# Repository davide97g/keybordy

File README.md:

# keybordy

A small keyboard built on a classic ESP32 DevKit: eight MX-style switches wired with jumpers only, and a rotary encoder to add later.

- `firmware/keys8/`: current firmware. Reads 8 keys, acts as a Bluetooth LE keyboard named `keybordy` that presses F13–F20, and prints `key N down` / `key N up` on serial at 115200. Also holds the Wokwi `diagram.json`.
- `host/`: Mac side. Hammerspoon maps F13–F20 to actions and serves a keymap editor on http://localhost:7373 (`host/ui/`).
- `firmware/switches_oled/`, `firmware/rotary_oled/`: earlier sketches with the SSD1306 OLED.
- `sim/`: fully local simulator, a vendored fork of Velxio (AGPLv3) in Docker, with a local Postgres for saved projects. Run `just sim-fetch-qemu` once, then `just sim-up` and open http://localhost:3080/editor?project=keys8. See `sim/README.md`.
- `pcb/`: rev A carrier PCB (KiCad 10, generated by `pcb/build.py`). Hotswap sockets for the 8 keys, female headers for the DevKit, OLED and rotary. Pin map, paper check and JLCPCB ordering steps are in `pcb/README.md`.
- `docs/`: board and bench notes.
- `guide/`: interactive wiring guide (Vite + React).

## Tooling

Tasks live in the root `justfile` (`just` lists them); tool versions are pinned in `mise.toml` (Bun, Node, Python, uv, just). Frontends use Bun (`bun.lock`), the simulator backend uses uv (`uv.lock`).

```
just install         # bun + uv dependencies
just dev             # simulator with backend hot reload + UI on http://localhost:5173
just test            # backend (incl. Postgres) + frontend tests
just fw-flash        # compile and flash keys8
```

## Wiring

No breadboard, so every board pin takes one jumper and each switch gets two pins: leg A to an input with the internal pull-up, leg B to ground. K1 uses a real `GND` pin. K2–K8 use GPIOs the firmware holds LOW.

| Key | Leg A | Leg B |
|---|---|---|
| K1 | GPIO32 | GND |
| K2 | GPIO33 | GPIO25 |
| K3 | GPIO14 | GPIO26 |
| K4 | GPIO13 | GPIO27 |
| K5 | GPIO4 | GPIO16 |
| K6 | GPIO18 | GPIO17 |
| K7 | GPIO19 | GPIO21 |
| K8 | GPIO23 | GPIO22 |
| Rotary (later) | CLK 34, DT 35, SW 39 | `+` to 3V3, GND to the second GND |

## Actions on the Mac

No server to run and no USB needed once flashed: the board only needs power (USB charger or power bank). It pairs as a Bluetooth keyboard, and Hammerspoon turns each key into an action.

1. `just fw-flash`, then power the board anywhere in Bluetooth range.
2. System Settings > Bluetooth: connect `keybordy` (no PIN). The Mac reconnects on its own after that.
3. `just host-install`: installs Hammerspoon into `~/Applications` (no sudo), links `host/hammerspoon/keybordy.lua` into `~/.hammerspoon`, starts it.
4. `just keymap` (or the ⌨︎ menu-bar item > Open keymap editor) opens http://localhost:7373.

The keymap editor shows the eight caps with their current action, lets you pick an action per key and try it before saving: ▶ on a cap (or Test) simulates a press with the unsaved version, and Activity lists every press, real or simulated, with the command output or the error. Save (⌘S) writes `~/.config/keybordy/keymap.json`; hand edits to that file load live too. `host/keymap.default.json` seeds it on first run.

| Action | Does | |
|---|---|---|
| Open app | launch or focus an app (picker with icons) | |
| Terminal | new Ghostty window in a folder, typing a command such as `claude` | |
| Shell command | `zsh -lc` in the background, output in Activity | |
| Open URL | any URL or app scheme (`obsidian://`, `raycast://`) | |
| Shortcut | `shortcuts run <name>` from the Shortcuts app | |
| Key combo | send e.g. ⇧⌘4 to the frontmost app (recorder included) | Accessibility |
| Type text | type a snippet | Accessibility |
| Media key | play/pause, next, volume, brightness | Accessibility |

Hotkeys need no permission. The last three need Hammerspoon in System Settings > Privacy & Security > Accessibility; the editor's `accessibility off · allow` chip opens that prompt. The first Terminal action asks to let Hammerspoon control Ghostty.

The editor is served by Hammerspoon on loopback only. Because it can run shell commands, every API call needs the token embedded in its page, and requests with a foreign `Host` or `Origin` are refused.

## Flash

```
just fw-flash        # arduino-cli compile --upload -p /dev/cu.usbserial-0001 --fqbn esp32:esp32:esp32 firmware/keys8
just fw-monitor
```

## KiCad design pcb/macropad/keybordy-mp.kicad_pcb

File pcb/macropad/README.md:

# keybordy MP PCB, rev A

A 2-layer board, 126.3 × 131.06 mm, for the keybordy MP macropad (`docs/macropad.md`). It is generated from `layout/macropad.json` and `layout/pins.json` by `build.py`. The schematic is in that script too: `parts()` lists every footprint with its pads' nets.

```sh
just mp-pcb          # place, Freerouting (5–20 min), DRC, then fab files into pcb/macropad/fab/
just mp-pcb-fab      # DRC + fab files only, after editing the board by hand in KiCad
just mp-pcb-open     # open in KiCad 10
```

Routing uses Freerouting 1.9.0 (`~/.local/share/freerouting/freerouting-1.9.0.jar`, Java 21+). Version 2.5 oscillates on this board and leaves about 30 connections unrouted. 1.9 is not deterministic either: a run leaves 0 to about 7 connections, so `route` tries up to four times and keeps the best session. A few stubs round the 0.5 mm-pitch amp and charger pins are drawn by hand in `place()`. After routing, `pour` fills GND on both layers and adds stitching vias on a 4 mm grid, plus one in any pour fragment the grid missed. `fab` fails on any DRC error or unconnected item. Silkscreen warnings and one starved thermal (an encoder GND pin, which is also on a routed track) do not block it.

## What is on it

All SMD parts are on the bottom, the same side as the hotswap sockets, so JLCPCB assembles one side.

- ESP32-S3-WROOM-1-N16R8. The antenna is flush with the rear edge, with no copper over it or within 15 mm either side.
- USB-C (USB 2.0) with 5.1k CC pull-downs and USBLC6 ESD protection.
- BQ24075 power-path charger.
  - Input limit about 860 mA (RILIM 1.8k). Charge current about 490 mA (RISET 1.8k).
  - TS has a fixed 10k because the cell has no NTC. Safety timer at its default.
  - The PWR switch drives SYSOFF. Off disconnects the battery; USB still powers the board, but the BQ24075 does not charge while SYSOFF is high, so leave PWR on to charge.
- AP2112K 3.3 V LDO, fed from the charger's OUT.
- MAX98357A amp on OUT, next to the speaker pads. GPIO46 drives SD_MODE high, which selects the left channel.
- ICS-43434 mic. Its port is a hole through the board under the deck's mic hole.
  - The MIC switch feeds its VDD from 3V3, or grounds it.
  - 1k resistors on its WS and SCK limit the current into it while it is off and the amp is using the shared clocks.
- Reverse-mount red LED on GPIO45, shining up through its hole.
- 22 Kailh hotswap sockets with 1N4148W diodes (COL2ROW).
- 3 encoders. A/B have 10k pull-ups. Each push has a diode into matrix row 4.
- BOOT and RST buttons. They are on the bottom, so they are only reachable with the case open. Normal flashing over native USB needs neither.
- Battery voltage on GPIO1 through a 100k/100k divider. Charge status on GPIO44.

## Ordering at JLCPCB

1. Upload `fab/keybordy-mp-gerbers.zip`. The viewer should show 2 layers and 126.3 × 131.06 mm. Keep FR-4, 1.6 mm, 1 oz and HASL lead-free.
2. Turn on PCB Assembly and choose the **Bottom side**. If Economic will not take a bottom-side job, pick Standard.
3. Assembly quantity: 2 is the minimum. Upload `fab/keybordy-mp-bom.csv` and `fab/keybordy-mp-cpl.csv`.
4. In the placement preview, check every polarised part against its silkscreen dot or bar before paying. JLC's rotation offsets differ from KiCad's. Check:
   - U1 to U6, pin 1.
   - D1–D33, cathode bar toward the row net.
   - D30, the LED.
   - J1, the USB-C mouth at the rear edge.
   - J2, the battery connector. Its opening faces the battery.
5. Stock risks as of 2026-10-07:
   - ICS-43434 (C5656610): about 1.4k in stock.
   - The ESP32-S3 module shows 0 at LCSC but 28k in JLC's own assembly stock.
   - Every IC is an Extended part, so each one adds a loading fee.

The BOM leaves out the parts you solder yourself, listed below.

## Solder yourself

| Part | Where | Notes |
|---|---|---|
| 3 × encoder | top, E1–E3 | Bourns PEC11R-4220F-S0024 (LCSC C143797, only a few hundred in stock). The footprint's lug slots also take Alps EC11 encoders such as the Amazon bench ones. |
| OLED, 7 wires | top, J3 at the rear edge | Cut the dupont ends off the Waveshare GH1.25 cable and solder the wires straight in. Pad order is `3V3 GND DIN CLK CS DC RST`, as on the silk. A header does not fit under the plate (3.5 mm). |
| Speaker, 2 wires | top, J4 at the left edge, `+` marked | Cut the PH1.25 plug off. |
| 22 × MX switch | top | They plug into the sockets. No soldering. |
| 2u stabilizer | top, K21 | Cherry PCB screw-in. |
| LiPo | bottom, J2 (JST PH 2.0) | **Check the polarity against the `+` and `-` on the silk before you plug it in.** Amazon cells come wired both ways, and the charger has no reverse-polarity protection. |

## Changes the case needs

- PWR switch moved from x 30 to x 68 in the layout, to the right of the USB-C. At x 30 it collided with the ESP32 module, and it was inside the antenna keep-out. `cad/` reads the layout, so `just cad-build` moves the tray's rear-wall slot. A tray printed before this change has the slot in the wrong place.
- The USB-C mouth sits 0.5 mm past the PCB edge, against the inside of the 3 mm wall. A plug's overmold is about 12.4 × 6.5 mm, so the 10 × 4.2 wall cut-out lets the plug in only about 3.5 mm. To seat the plug fully, widen the cut-out or recess the wall around it.
- The slide-switch levers stick out about 0.85 mm past the PCB edge, which doesn't reach through a 3 mm wall. Thin the wall at the two switch slots, or print a small slider.

## Not verified

- This board is untested. Nothing on it has been through the bench prototype (phase 1) yet. The charger, amp and mic circuits follow their datasheets' typical application circuits.
- The netlist was checked against KiCad's symbol pinouts. There is no separate schematic, so KiCad's ERC never ran.
- The Waveshare OLED's pin order and the speaker plug's wiring come from the listings, not from the parts in hand.

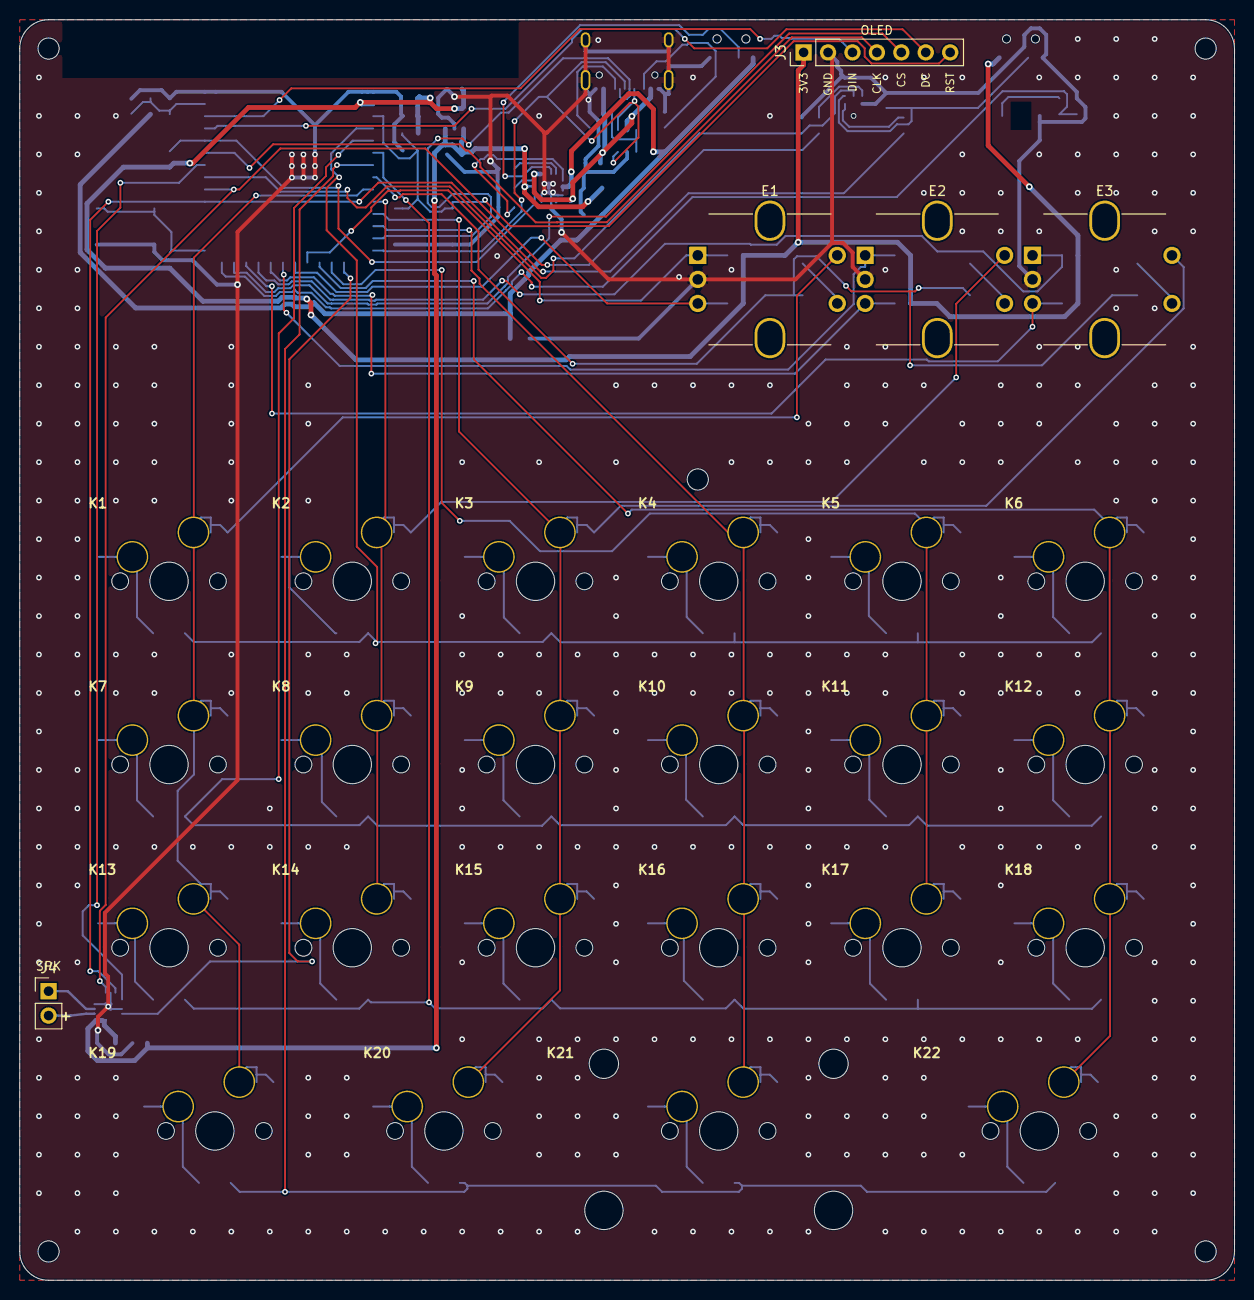
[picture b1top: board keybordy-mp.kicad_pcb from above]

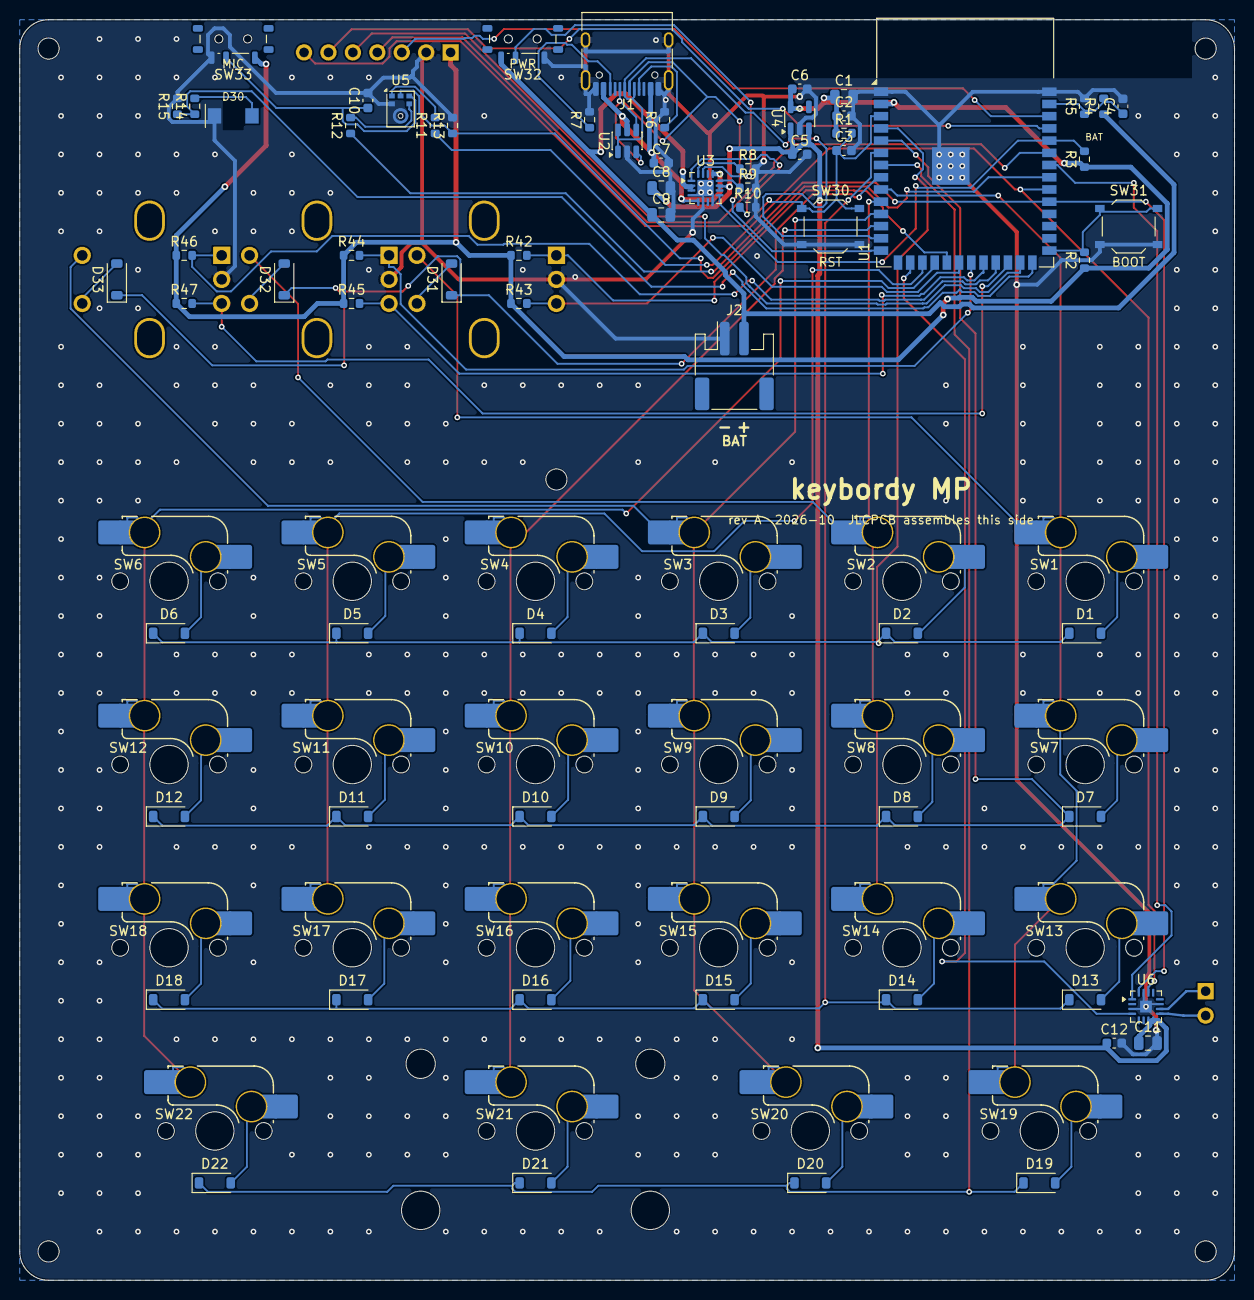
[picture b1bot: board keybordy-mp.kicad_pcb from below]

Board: 2 copper layers, 126.3 x 131.1 mm, 107 parts (93 on the bottom side), 75 nets.

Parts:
C1, C8, C9, C11: 10uF; C_0805_2012Metric
C2, C4, C10, C12: 100nF; C_0603_1608Metric
C3, C5, C6: 1uF; C_0603_1608Metric
C7: 4.7uF; C_0603_1608Metric
D1, D2, D3, D4, D5, D6, D7, D8, D9, D10, D11, D12, D13, D14, D15, D16, D17, D18, D19, D20, D21, D22, D31, D32, D33: 1N4148W; D_SOD-123
D30: LTST-C230KRKT; LED_1206_ReverseMount_LiteOn
E1, E2, E3: PEC11R-4220F-S0024; RotaryEncoder_Bourns_PEC11R_Vertical
H1, H2, H3, H4, H5: M2; MountingHole_2.2mm_M2
J1: TYPE-C-31-M-12; USB_C_Receptacle_HRO_TYPE-C-31-M-12
J2: S2B-PH-SM4-TB; JST_PH_S2B-PH-SM4-TB_1x02-1MP_P2.00mm_Horizontal
J3: OLED wires; PinHeader_1x07_P2.54mm_Vertical
J4: Speaker wires; PinHeader_1x02_P2.54mm_Vertical
R1, R2, R3, R10, R42, R43, R44, R45, R46, R47: 10k; R_0603_1608Metric
R4, R5, R13, R15: 100k; R_0603_1608Metric
R6, R7: 5.1k; R_0603_1608Metric
R8, R9: 1.8k; R_0603_1608Metric
R11, R12, R14: 1k; R_0603_1608Metric
ST1, ST2, ST3, ST4: stab; MountingHole_2.2mm_M2
SW1, SW2, SW3, SW4, SW5, SW6, SW7, SW8, SW9, SW10, SW11, SW12, SW13, SW14, SW15, SW16, SW17, SW18, SW19, SW20, SW21, SW22: Kailh MX hotswap; SW_MX_HS_CPG151101S11_1u
SW30, SW31: TS-1187A; SW_Push_1P1T_XKB_TS-1187A
SW32, SW33: MSK12C02; SW_SPDT_Shouhan_MSK12C02
U1: ESP32-S3-WROOM-1-N16R8; ESP32-S3-WROOM-1
U2: USBLC6-2SC6; SOT-23-6
U3: BQ24075RGTR; VQFN-16-1EP_3x3mm_P0.5mm_EP1.68x1.68mm
U4: AP2112K-3.3; SOT-23-5
U5: ICS-43434; InvenSense_ICS-43434-6_3.5x2.65mm
U6: MAX98357AETE+T; TQFN-16-1EP_3x3mm_P0.5mm_EP1.23x1.23mm

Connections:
+3V3: C1.1, C2.1, C6.1, J3.1, R1.1, R2.1, R3.1, R42.1, R43.1, R44.1, R45.1, R46.1, R47.1, SW33.1, U1.2, U4.5
AMP_DIN: U1.34, U6.1
AMP_SD: U1.16, U6.4
BOOT: R2.2, SW31.1, U1.27
CHG_N: R3.2, U1.36, U3.9
COL0: E1.S1, SW1.2, SW7.2, SW13.2, SW19.2, U1.9
COL1: E2.S1, SW2.2, SW8.2, SW14.2, U1.10
COL2: E3.S1, SW3.2, SW9.2, SW15.2, SW20.2, U1.11
COL3: SW4.2, SW10.2, SW16.2, SW21.2, U1.12
COL4: SW5.2, SW11.2, SW17.2, U1.17
COL5: SW6.2, SW12.2, SW18.2, SW22.2, U1.18
E1A: E1.A, R42.2, U1.19
E1B: E1.B, R43.2, U1.20
E2A: E2.A, R44.2, U1.21
E2B: E2.B, R45.2, U1.22
E3A: E3.A, R46.2, U1.23
E3B: E3.B, R47.2, U1.24
ED1: D31.2, E1.S2
ED2: D32.2, E2.S2
ED3: D33.2, E3.S2
EN: C3.1, J3.7, R1.2, SW30.1, U1.3
GND: C1.2, C2.2, C3.2, C4.2, C5.2, C6.2, C7.2, C8.2, C9.2, C10.2, C11.2, C12.2, D30.1, E1.C, E2.C, E3.C, J1.A1, J1.A12, J1.B1, J1.B12, J1.SH, J2.1, J3.2, R5.2, R6.2, R7.2, R8.2, R9.2, R10.2, R13.2, R15.2, SW30.2, SW31.2, SW32.1, SW33.3, U1.1, U1.40, U1.41, U2.2, U3.4, U3.6, U3.8, U3.17, U4.2, U5.2, U5.3, U6.3, U6.11, U6.15, U6.17
I2S_BCLK: R12.1, U1.31, U6.16
I2S_WS: R11.1, U1.32, U6.14
ILIM: R9.1, U3.12
ISET: R8.1, U3.16
KD1: D1.2, SW1.1
KD2: D2.2, SW2.1
KD3: D3.2, SW3.1
KD4: D4.2, SW4.1
KD5: D5.2, SW5.1
KD6: D6.2, SW6.1
KD7: D7.2, SW7.1
KD8: D8.2, SW8.1
KD9: D9.2, SW9.1
KD10: D10.2, SW10.1
KD11: D11.2, SW11.1
KD12: D12.2, SW12.1
KD13: D13.2, SW13.1
KD14: D14.2, SW14.1
KD15: D15.2, SW15.1
KD16: D16.2, SW16.1
KD17: D17.2, SW17.1
KD18: D18.2, SW18.1
KD19: D19.2, SW19.1
KD20: D20.2, SW20.1
KD21: D21.2, SW21.1
KD22: D22.2, SW22.1
LED_A: D30.2, R14.2
MIC_LED: R14.1, R15.1, U1.26
MIC_SCK: R12.2, U5.4
MIC_SD: R13.1, U1.33, U5.6
MIC_VDD: C10.1, SW33.2, U5.5
MIC_WS: R11.2, U5.1
OLED_CS: J3.5, U1.25
OLED_DC: J3.6, U1.37
OLED_MOSI: J3.3, U1.38
OLED_SCK: J3.4, U1.35
ROW0: D1.1, D2.1, D3.1, D4.1, D5.1, D6.1, U1.4
ROW1: D7.1, D8.1, D9.1, D10.1, D11.1, D12.1, U1.5
ROW2: D13.1, D14.1, D15.1, D16.1, D17.1, D18.1, U1.6
ROW3: D19.1, D20.1, D21.1, D22.1, U1.7
ROW4: D31.1, D32.1, D33.1, U1.8
SPK_N: J4.1, U6.10
SPK_P: J4.2, U6.9
SYSOFF: SW32.2, U3.15
TS: R10.1, U3.1
USB_CC1: J1.A5, R6.1
USB_CC2: J1.B5, R7.1
USB_DN: J1.A7, J1.B7, U1.13, U2.1, U2.6
USB_DP: J1.A6, J1.B6, U1.14, U2.3, U2.4
VBAT: C9.1, J2.2, R4.1, SW32.3, U3.2, U3.3
VBAT_ADC: C4.1, R4.2, R5.1, U1.39
VBUS: C7.1, J1.A4, J1.A9, J1.B4, J1.B9, U2.5, U3.5, U3.13
VSYS: C5.1, C8.1, C11.1, C12.1, U3.10, U3.11, U4.1, U4.3, U6.7, U6.8

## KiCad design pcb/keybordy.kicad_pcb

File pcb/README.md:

# keybordy PCB, rev A

A 2-layer carrier board, 111.5 × 72.6 mm. The ESP32 DevKit, the OLED and the rotary module plug into female headers. The eight MX switches go into Kailh hotswap sockets on the back. Every switch has a real GND through the ground pour, so no GPIO is used as a ground. That frees enough pins for the OLED and the rotary.

`build.py` generates the board (`keybordy.kicad_pcb`), with every coordinate written in the script. It needs no autorouter. `just pcb-build` regenerates the board, routes it, runs DRC and writes the fab files to `pcb/fab/` (gitignored). `just pcb-open` opens the board in KiCad 10, installed in `~/Applications/KiCad`. If you edit the board by hand in KiCad, `just pcb-build` overwrites those edits, so run `just pcb-fab` afterwards instead.

| File in `pcb/fab/` | Use |
|---|---|
| `keybordy-gerbers.zip` | upload this to the fab |
| `print-1to1-top.pdf` | print at 100 % to check the fit on paper |
| `render-top.png`, `render-bottom.png` | 3D previews |
| `drc.json` | DRC report: 0 violations, 0 unconnected |

## Pin map

This map differs from the jumper rig in `firmware/keys8`. The key pins are the eight usable pins on the DevKit row nearest the keys, so the tracks fan out without crossings.

| Part | Signal | GPIO (DevKit label) |
|---|---|---|
| K1 / K2 / K3 / K4 (top row) | leg A | 16 (RX2) / 18 / 21 / 23 |
| K5 / K6 / K7 / K8 (bottom row) | leg A | 4 / 17 (TX2) / 19 / 22 |
| all keys | leg B | GND |
| OLED | SDA / SCL | 33 / 32 |
| OLED | VCC / GND | 3V3 / GND |
| Rotary | CLK / DT / SW | 35 / 34 / 39 (VN) |
| Rotary | + / GND | 3V3 / GND |

Firmware for this board needs:

```cpp
static const int KEY_PINS[] = {16, 18, 21, 23, 4, 17, 19, 22};
// no GND_PINS: every switch is on the GND pour
Wire.begin(33, 32);                      // SDA, SCL
// rotary: CLK 35, DT 34, SW 39, pull-ups on the module
```

`keys8` as it is will not read the keys on this board, because its key pins are different.

## Before you order: check on paper

1. Print `pcb/fab/print-1to1-top.pdf` at 100 % ("actual size", not "fit to page"). Measure the board outline on paper. It must be 111.5 mm wide.
2. Lay the DevKit on the print chip up, with USB at the `USB` mark. Every DevKit pin must sit on a pad, and the DevKit's own labels must match the silkscreen labels: `VIN` over `VIN`, `3V3` over `3V3`. If they are mirrored, stop: the board is wrong for your DevKit.
3. Check that the rows are 25.4 mm apart (10 holes on perfboard). If yours are 22.86 mm, change `DEVKIT_ROW_SPACING` in `build.py` and run `just pcb-build`.
4. Check the pin order printed on the OLED (`GND VCC SCL SDA`) and on the rotary (`CLK DT SW + GND`) against the silkscreen.

## Ordering at JLCPCB

1. Open jlcpcb.com, go to "Order now" and upload `pcb/fab/keybordy-gerbers.zip`. The viewer should show 2 layers and 111.5 × 72.6 mm.
2. Keep the defaults: FR-4, 2 layers, 1.6 mm thick, 1 oz copper, HASL (lead-free costs a little more), quantity 5. Any colour works; green ships fastest.
3. Under "Mark on PCB", choose "Remove Mark" if you don't want JLC's order number printed on the silkscreen. It costs a little extra.
4. Leave PCB Assembly off. Every part is hand-soldered.
5. Pay and pick shipping. Tax for Italy/EU is charged at checkout (IOSS), so nothing is due on delivery.

PCBWay (pcbway.com) and Aisler (aisler.net, made in Germany, no customs) accept the same zip. Aisler can also take `keybordy.kicad_pcb` directly.

## Parts to buy

| Qty | Part |
|---|---|
| 8 (+2 spare) | Kailh MX hotswap socket (CPG151101S11) |
| 2 | female header 1×15, 2.54 mm, vertical (DevKit) |
| 1 | female header 1×4, 2.54 mm, vertical (OLED) |
| 1 | female header 1×5, 2.54 mm, right angle (rotary) |
| 5 | M2 screws + standoffs, optional, for a case or plate |

Without a plate, 3-pin switches sit loosely in hotswap sockets. A 3D-printed plate 5 mm above the PCB, the standard MX height, holds them. The M2 holes are there for it.

## Assembly order

1. Hotswap sockets on the back. Tin one pad, slide the socket in with tweezers, reflow the pad, then solder the other pad.
2. DevKit headers on the front. Plug both headers onto the DevKit first, then solder them with the DevKit in place, so the rows stay parallel and at the right spacing.
3. OLED header and rotary right-angle header, the same way, with the module plugged in.
4. Flash the PCB firmware, then plug the DevKit in.

## Credits

`keybordy.pretty/SW_MX_HS_CPG151101S11_1u.kicad_mod` comes from [marbastlib](https://github.com/ebastler/marbastlib) by ebastler and is licensed CERN-OHL-P v2. Every other footprint ships with KiCad.

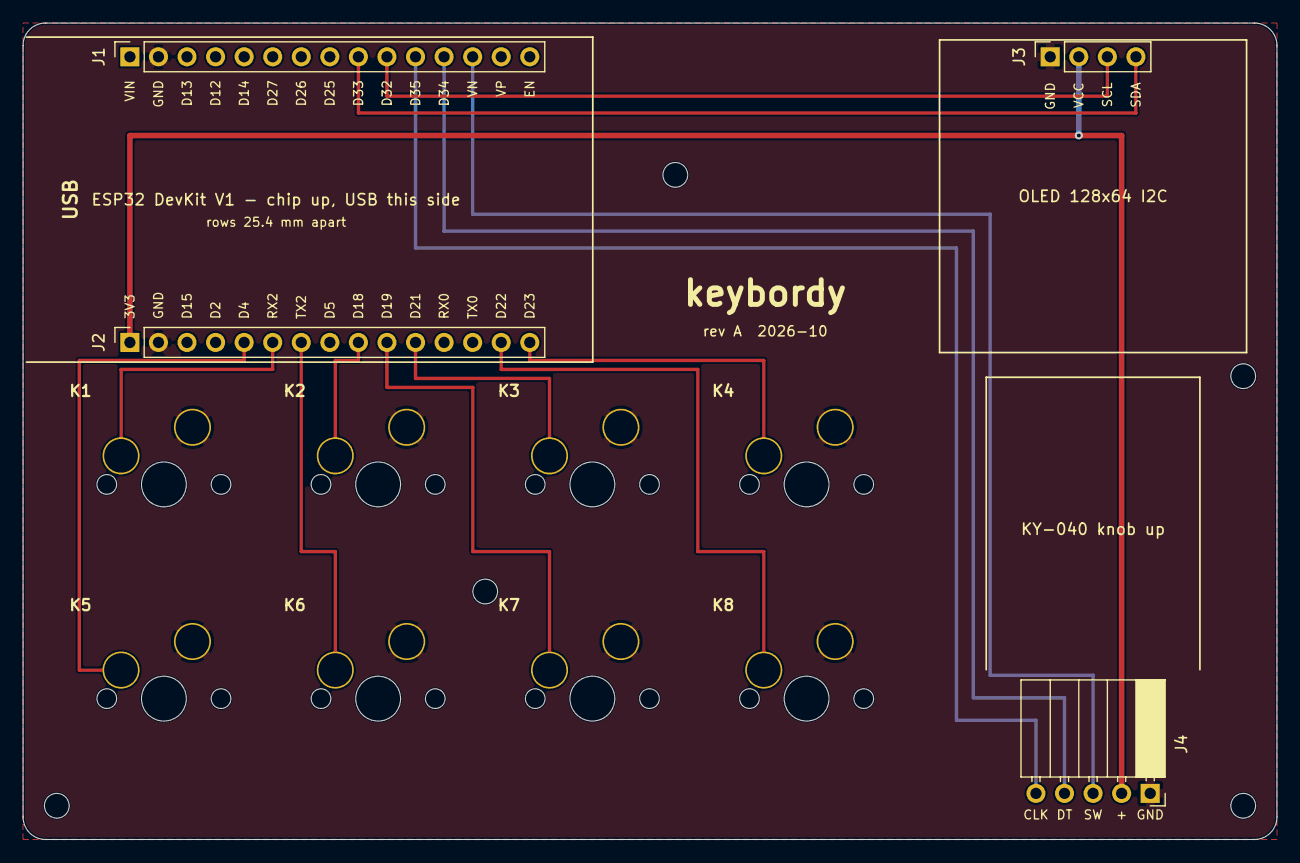
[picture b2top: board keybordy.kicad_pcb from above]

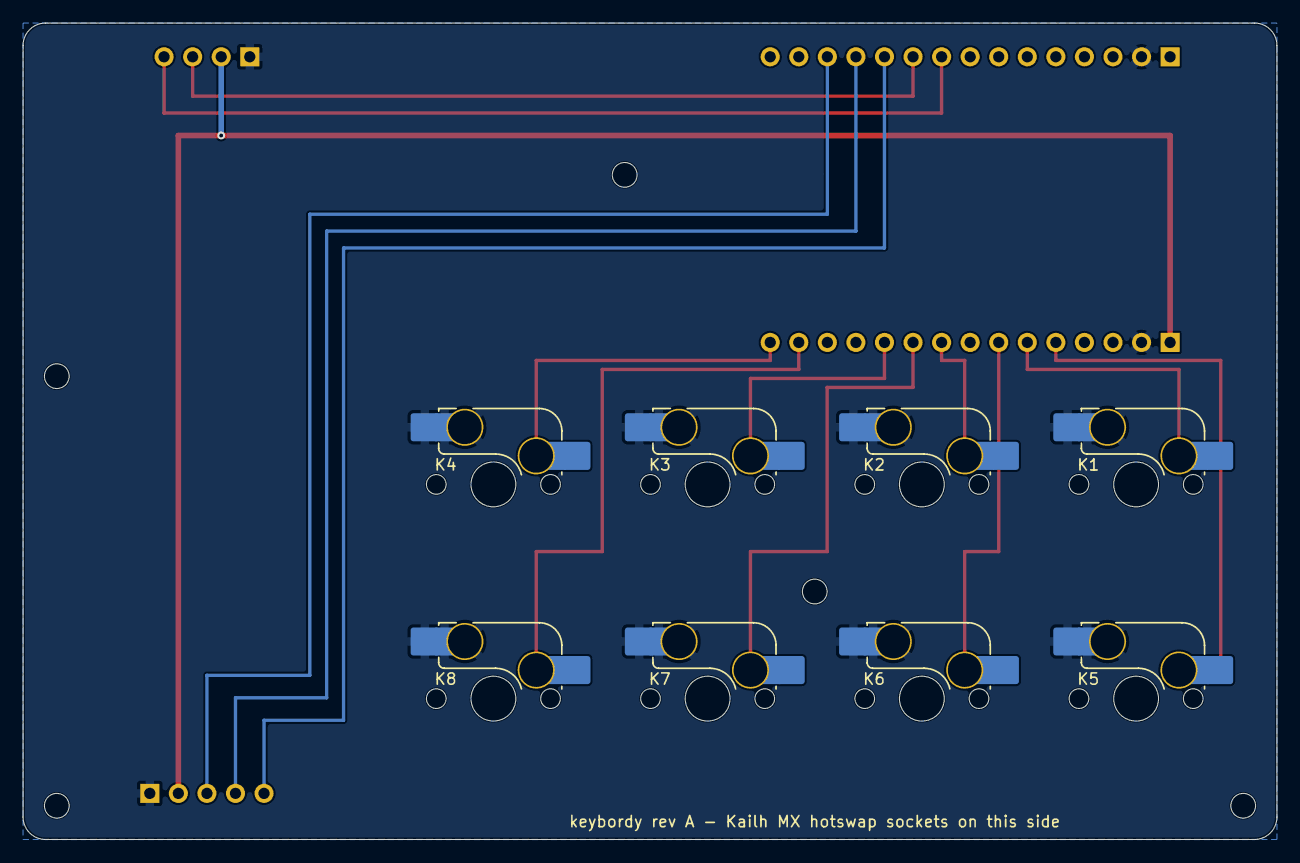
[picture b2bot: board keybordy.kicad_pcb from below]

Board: 2 copper layers, 111.5 x 72.6 mm, 17 parts (8 on the bottom side), 15 nets.

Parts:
H1, H2, H3, H4, H5: M2; MountingHole_2.2mm_M2
J1: DevKit top row; PinSocket_1x15_P2.54mm_Vertical
J2: DevKit bottom row; PinSocket_1x15_P2.54mm_Vertical
J3: SSD1306 OLED; PinSocket_1x04_P2.54mm_Vertical
J4: KY-040 rotary; PinSocket_1x05_P2.54mm_Horizontal
K1, K2, K3, K4, K5, K6, K7, K8: Kailh MX hotswap; SW_MX_HS_CPG151101S11_1u

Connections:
+3V3: J2.1, J3.2, J4.2
GND: J1.2, J2.2, J3.1, J4.1, K1.2, K2.2, K3.2, K4.2, K5.2, K6.2, K7.2, K8.2
KEY1: J2.6, K1.1
KEY2: J2.9, K2.1
KEY3: J2.11, K3.1
KEY4: J2.15, K4.1
KEY5: J2.5, K5.1
KEY6: J2.7, K6.1
KEY7: J2.10, K7.1
KEY8: J2.14, K8.1
OLED_SCL: J1.10, J3.3
OLED_SDA: J1.9, J3.4
ROT_CLK: J1.11, J4.5
ROT_DT: J1.12, J4.4
ROT_SW: J1.13, J4.3

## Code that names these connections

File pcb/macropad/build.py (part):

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# Pour and routing classes: (track mm, clearance mm, net patterns).
NETCLASSES = {
    "Power": (0.5, 0.2, ["VBUS", "VSYS", "VBAT", "+3V3"]),
    "Speaker": (0.25, 0.2, ["SPK_P", "SPK_N"]),    # 0.5 mm-pitch amp pins
    "Ground": (0.4, 0.2, ["GND"]),
}

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        by_gpio[ab["a"]] = f"{e}A"
        by_gpio[ab["b"]] = f"{e}B"
    i2s = P["i2s"]
    by_gpio.update({i2s["bclk"]: "I2S_BCLK", i2s["ws"]: "I2S_WS", i2s["mic_sd"]: "MIC_SD", i2s["amp_din"]: "AMP_DIN"})
    by_gpio[gpio(P["amp_sd"])] = "AMP_SD"
    o = P["oled"]
    by_gpio.update({gpio(o["sck"]): "OLED_SCK", gpio(o["mosi"]): "OLED_MOSI", gpio(o["cs"]): "OLED_CS",
                    gpio(o["dc"]): "OLED_DC"})
    by_gpio[gpio(P["vbat_adc"])] = "VBAT_ADC"
    by_gpio[gpio(P["charge_stat"])] = "CHG_N"
    by_gpio[gpio(P["mic_led"])] = "MIC_LED"
    by_gpio[gpio(P["boot_button"])] = "BOOT"
    by_gpio.update({19: "USB_DN", 20: "USB_DP"})
    if o["res"] != "EN":
        sys.exit("pins.json: OLED RES is expected on EN")
    pads = {1: "GND", 40: "GND", 41: "GND", 2: "+3V3", 3: "EN"}
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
